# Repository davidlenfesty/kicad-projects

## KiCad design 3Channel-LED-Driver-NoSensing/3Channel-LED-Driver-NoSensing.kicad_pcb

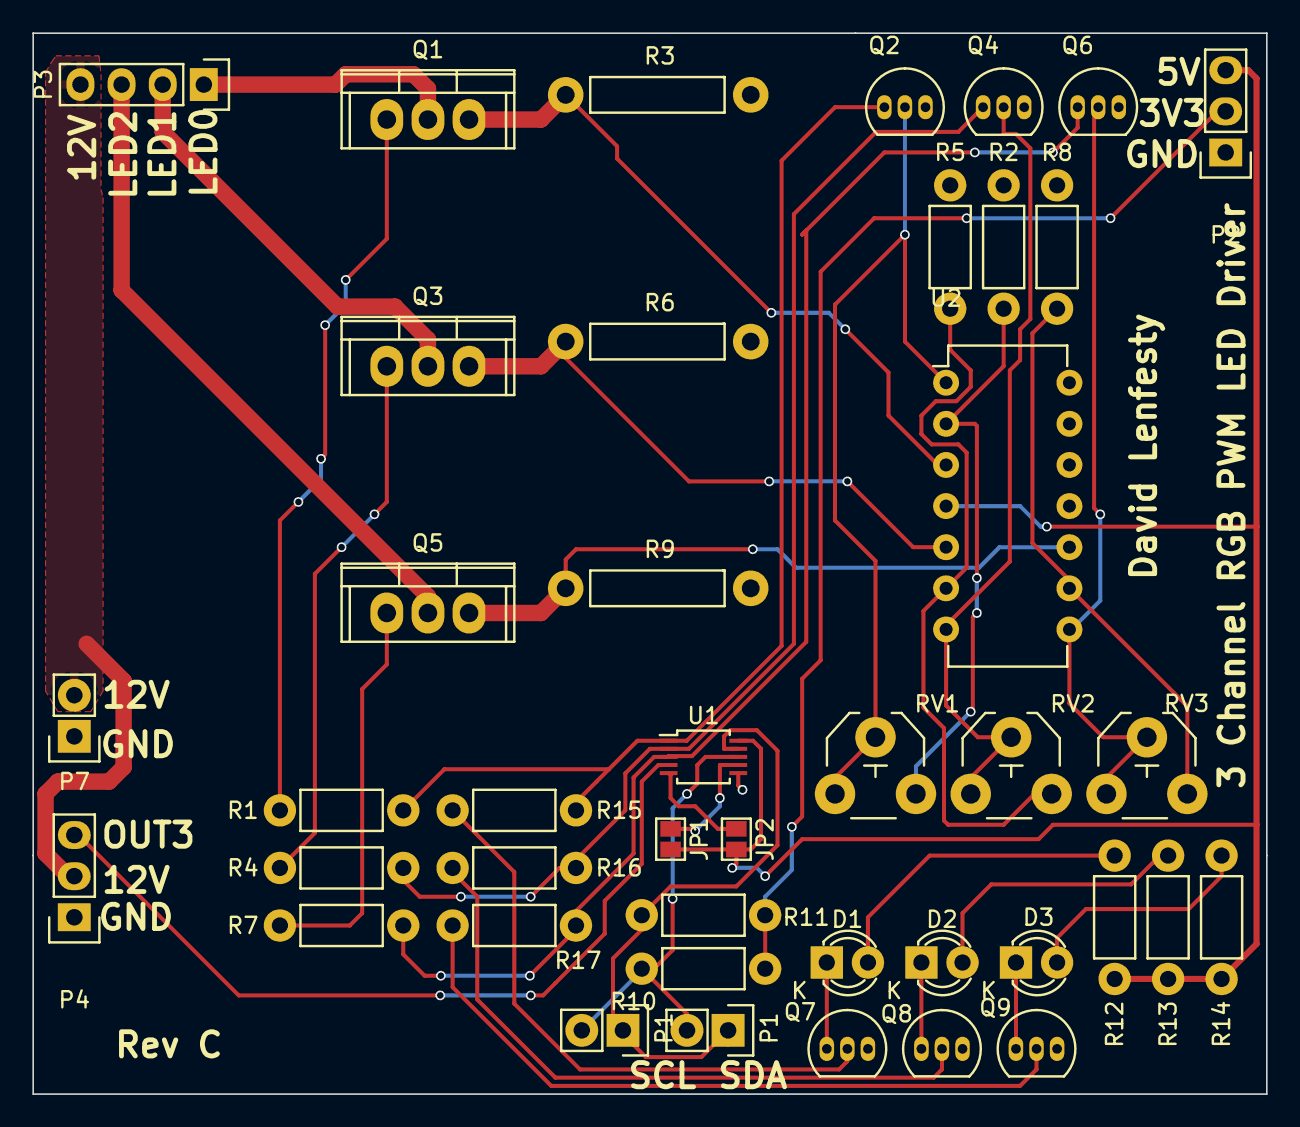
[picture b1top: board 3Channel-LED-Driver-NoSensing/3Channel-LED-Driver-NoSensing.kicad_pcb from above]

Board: 2 copper layers, 76.2 x 65.5 mm, 42 parts (0 on the bottom side), 36 nets.

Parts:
D1, D2, D3: LED; LED-3MM
JP1, JP2: Jumper_NO_Small; GS2
P1, P1#2, P7: CONN_01X02; Pin_Header_Straight_1x02
P2, P4: CONN_01X03; Pin_Header_Straight_1x03
P3: CONN_01X04; Pin_Header_Straight_1x04
Q1, Q3, Q5: BUT11A; TO-220
Q2, Q4, Q6, Q7, Q8, Q9: BC413; TO-92_Inline_Narrow_Oval
R1, R4, R7: 10K; Resistor_Horizontal_RM7mm
R2, R5, R8: 2K; Resistor_Horizontal_RM7mm
R3, R6, R9: R; Current_Sense_Resistor
R10, R11: 4.7K; Resistor_Horizontal_RM7mm
R12, R13, R14: 330; Resistor_Horizontal_RM7mm
R15, R16, R17: 50K; Resistor_Horizontal_RM7mm
RV1, RV2, RV3: 10K; Potentiometer_VishaySpectrol-Econtrim-Type36P
U1: PCA9633; TSSOP-10_3x3mm_Pitch0.5mm
U2: LM324AN; DIP-14_W7.62mm

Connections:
+3V3: P2.2, R10.2, R11.2
+5V: JP1.2, JP2.2, P2.3, R12.2, R13.1, R14.1, U1.10, U2.4
+12V: P3.4, P4.2, P7.2
GND: P2.1, P4.1, P7.1, Q2.3, Q4.3, Q6.3, Q7.3, Q8.3, Q9.3, R2.2, R3.2, R5.2, R6.2, R8.2, R9.2, U1.6, U2.11
LED0_IND: Q2.1, R1.2, R15.2, U1.1
LED1_IND: Q4.1, R4.2, R16.2, U1.2
LED2_IND: Q6.1, R7.2, R17.2, U1.3
unnamed: D1.1, Q7.1
unnamed: D1.2, R12.1
unnamed: D2.1, Q8.1
unnamed: D2.2, R13.2
unnamed: D3.1, Q9.1
unnamed: D3.2, R14.2
unnamed: JP1.1, U1.7
unnamed: JP2.1, U1.5
unnamed: P1.1, P1#2.1, R11.1, U1.9
unnamed: P1.2, P1#2.2, R10.1, U1.8
unnamed: P3.1, Q1.2
unnamed: P3.2, Q3.2
unnamed: P3.3, Q5.2
unnamed: P4.3, U1.4
unnamed: Q1.1, R1.1
unnamed: Q1.3, R3.1, U2.3
unnamed: Q2.2, RV1.1, RV1.2, U2.1
unnamed: Q3.1, R4.1
unnamed: Q3.3, R6.1, U2.5
unnamed: Q4.2, RV2.1, RV2.2, U2.7
unnamed: Q5.1, R7.1
unnamed: Q5.3, R9.1, U2.10
unnamed: Q6.2, RV3.1, RV3.2, U2.8
unnamed: Q7.2, R15.1
unnamed: Q8.2, R16.1
unnamed: Q9.2, R17.1
unnamed: R2.1, RV1.3, U2.2
unnamed: R5.1, RV2.3, U2.6
unnamed: R8.1, RV3.3, U2.9

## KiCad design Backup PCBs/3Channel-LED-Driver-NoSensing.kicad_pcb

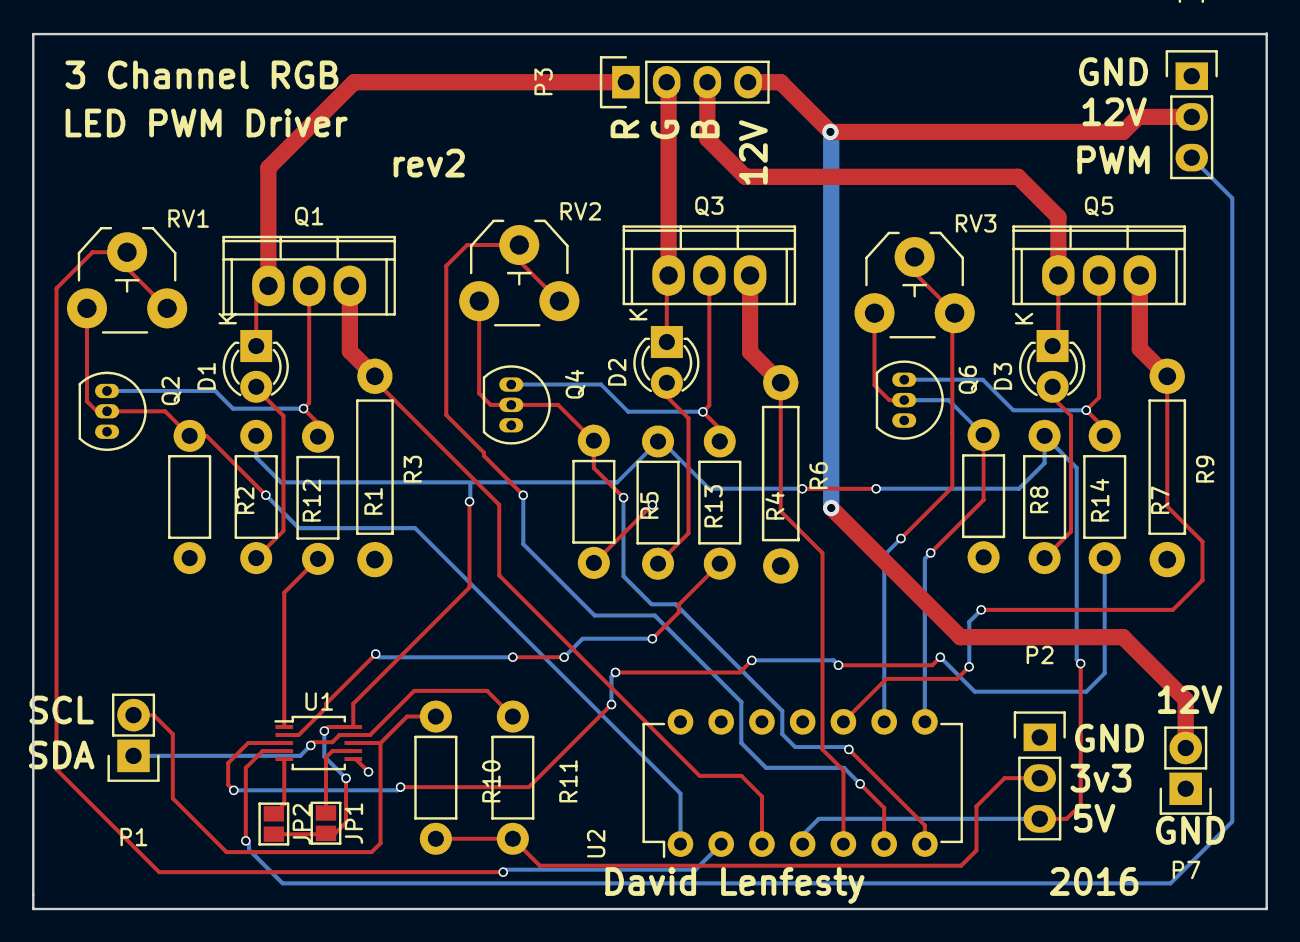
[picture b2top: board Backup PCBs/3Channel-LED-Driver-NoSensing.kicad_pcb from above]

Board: 2 copper layers, 76.9 x 54.6 mm, 35 parts (0 on the bottom side), 30 nets.

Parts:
D1, D2, D3: LED; LED-3MM
JP1, JP2: Jumper_NO_Small; GS2
P1, P7: CONN_01X02; Pin_Header_Straight_1x02
P2, P4: CONN_01X03; Pin_Header_Straight_1x03
P3: CONN_01X04; Pin_Header_Straight_1x04
Q1, Q3, Q5: BUZ11; TO-220
Q2, Q4, Q6: BC413; TO-92_Inline_Narrow_Oval
R1, R4, R7: 10K; Resistor_Horizontal_RM7mm
R2, R5, R8: 2K; Resistor_Horizontal_RM7mm
R3, R6, R9: R; Current_Sense_Resistor
R10, R11: 4.7K; Resistor_Horizontal_RM7mm
R12, R13, R14: 330; Resistor_Horizontal_RM7mm
RV1, RV2, RV3: 10K; Potentiometer_VishaySpectrol-Econtrim-Type36P
U1: PCA9633; TSSOP-10_3x3mm_Pitch0.5mm
U2: LM324AN; DIP-14_W7.62mm

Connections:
+3V3: P2.2, R10.2, R11.2
+5V: JP1.2, JP2.2, P2.3, R12.1, R13.1, R14.1, U1.10, U2.4
+12V: P3.4, P4.2, P7.2
GND: P2.1, P4.1, P7.1, Q2.3, Q4.3, Q6.3, R2.2, R3.2, R5.2, R6.2, R8.2, R9.2, U1.6, U2.11
unnamed: D1.1, P3.1, Q1.1
unnamed: D1.2, R12.2
unnamed: D2.1, P3.2, Q3.1
unnamed: D2.2, R13.2
unnamed: D3.1, P3.3, Q5.1
unnamed: D3.2, R14.2
unnamed: JP1.1, U1.7
unnamed: JP2.1, U1.5
unnamed: P1.1, R11.1, U1.9
unnamed: P1.2, R10.1, U1.8
unnamed: P4.3, U1.4
unnamed: Q1.2, Q2.1, R1.1
unnamed: Q1.3, R3.1, U2.3
unnamed: Q2.2, R2.1, RV1.1, U2.1
unnamed: Q3.2, Q4.1, R4.1
unnamed: Q3.3, R6.1, U2.5
unnamed: Q4.2, R5.1, RV2.1, U2.7
unnamed: Q5.2, Q6.1, R7.1
unnamed: Q5.3, R9.1, U2.10
unnamed: Q6.2, R8.1, RV3.1, U2.8
unnamed: R1.2, U1.1
unnamed: R4.2, U1.2
unnamed: R7.2, U1.3
unnamed: RV1.2, RV1.3, U2.2
unnamed: RV2.2, RV2.3, U2.6
unnamed: RV3.2, RV3.3, U2.9

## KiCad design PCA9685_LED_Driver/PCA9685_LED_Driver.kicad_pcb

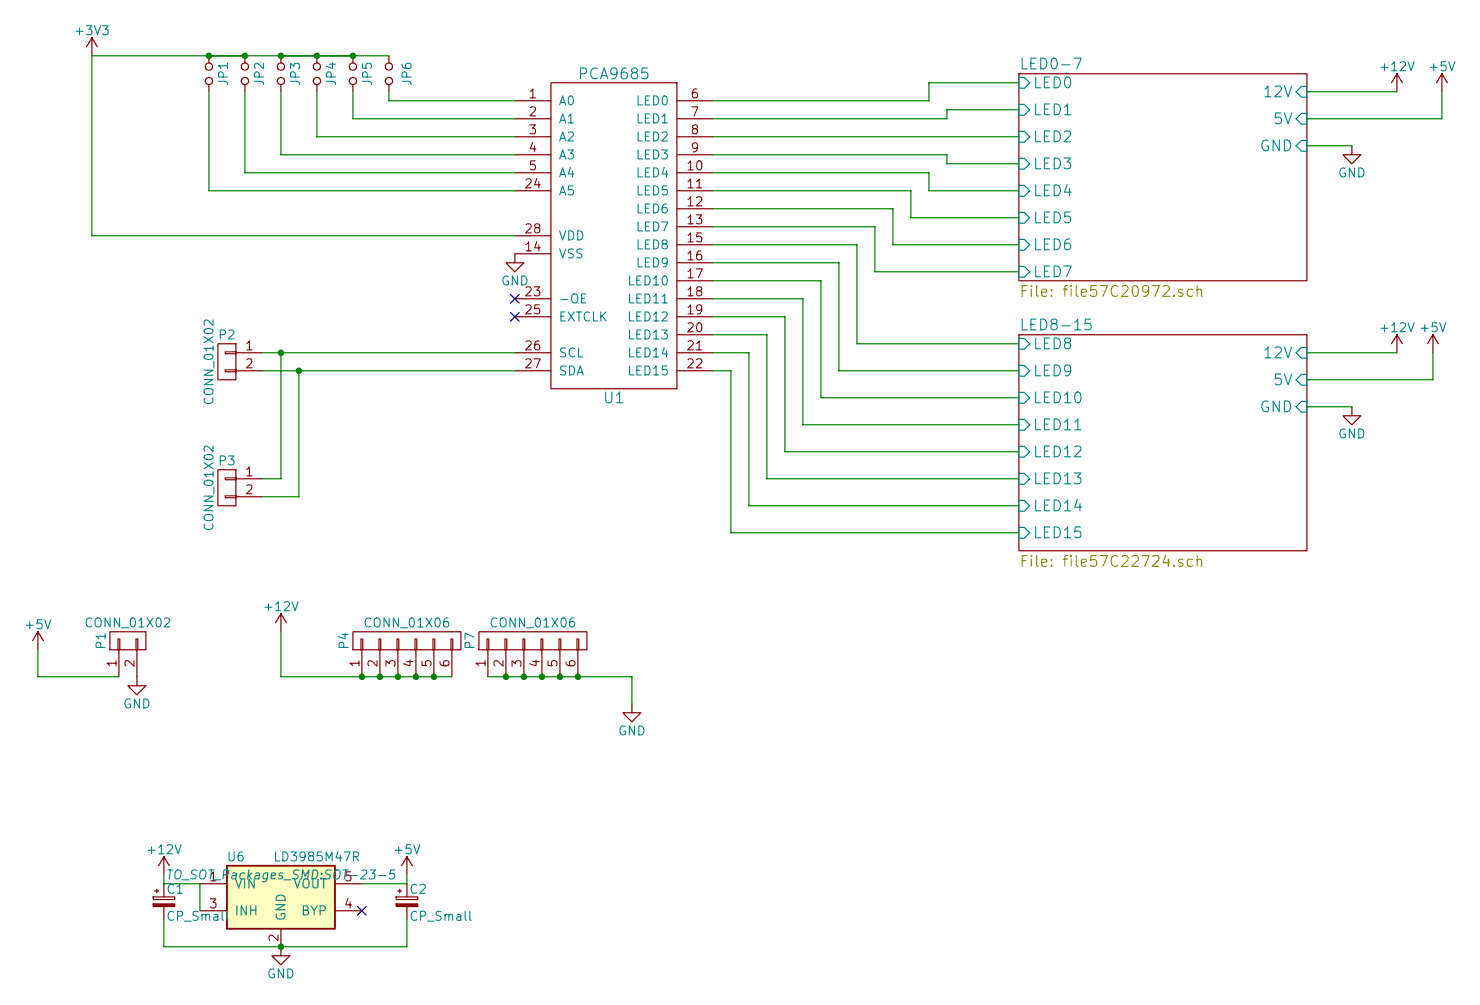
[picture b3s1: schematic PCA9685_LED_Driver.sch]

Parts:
C1, C2: CP_Small; TantalC_SizeA_EIA-3216_HandSoldering
JP1, JP2, JP3, JP4, JP5, JP6: Jumper_NO_Small; GS2
P1, P2, P3: CONN_01X02; Pin_Header_Straight_1x02
P4, P7: CONN_01X06; Screw_Connector_M5
U1: PCA9685; TSSOP-28_4.4x9.7mm_Pitch0.65mm
U6: LD3985M47R; SOT-23-5

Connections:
+3V3: JP1.1, JP2.1, JP3.1, JP4.1, JP5.1, JP6.1, U1.28 (VDD)
+5V: C2.1, P1.1, U6.5 (VOUT); also elsewhere on the board
+12V: C1.1, P4.1, P4.2, P4.3, P4.4, P4.5, P4.6, U6.1 (VIN), U6.3 (INH); also elsewhere on the board
/LED0-7/LED1: U1.7 (LED1); also elsewhere on the board
/LED0-7/LED2: U1.8 (LED2); also elsewhere on the board
/LED0-7/LED3: U1.9 (LED3); also elsewhere on the board
/LED0-7/LED4: U1.10 (LED4); also elsewhere on the board
/LED0-7/LED5: U1.11 (LED5); also elsewhere on the board
/LED0-7/LED6: U1.12 (LED6); also elsewhere on the board
/LED0-7/LED7: U1.13 (LED7); also elsewhere on the board
/LED8-15/LED8: U1.15 (LED8); also elsewhere on the board
/LED8-15/LED9: U1.16 (LED9); also elsewhere on the board
/LED8-15/LED10: U1.17 (LED10); also elsewhere on the board
/LED8-15/LED11: U1.18 (LED11); also elsewhere on the board
/LED8-15/LED12: U1.19 (LED12); also elsewhere on the board
/LED8-15/LED13: U1.20 (LED13); also elsewhere on the board
/LED8-15/LED14: U1.21 (LED14); also elsewhere on the board
/LED8-15/LED15: U1.22 (LED15); also elsewhere on the board
GND: C1.2, C2.2, P1.2, P7.1, P7.2, P7.3, P7.4, P7.5, P7.6, U1.14 (VSS), U6.2 (GND); also elsewhere on the board
unnamed: JP1.2, U1.24 (A5)
unnamed: JP2.2, U1.5 (A4)
unnamed: JP3.2, U1.4 (A3)
unnamed: JP4.2, U1.3 (A2)
unnamed: JP5.2, U1.2 (A1)
unnamed: JP6.2, U1.1 (A0)
unnamed: P2.1, P3.1, U1.26 (SCL)
unnamed: P2.2, P3.2, U1.27 (SDA)

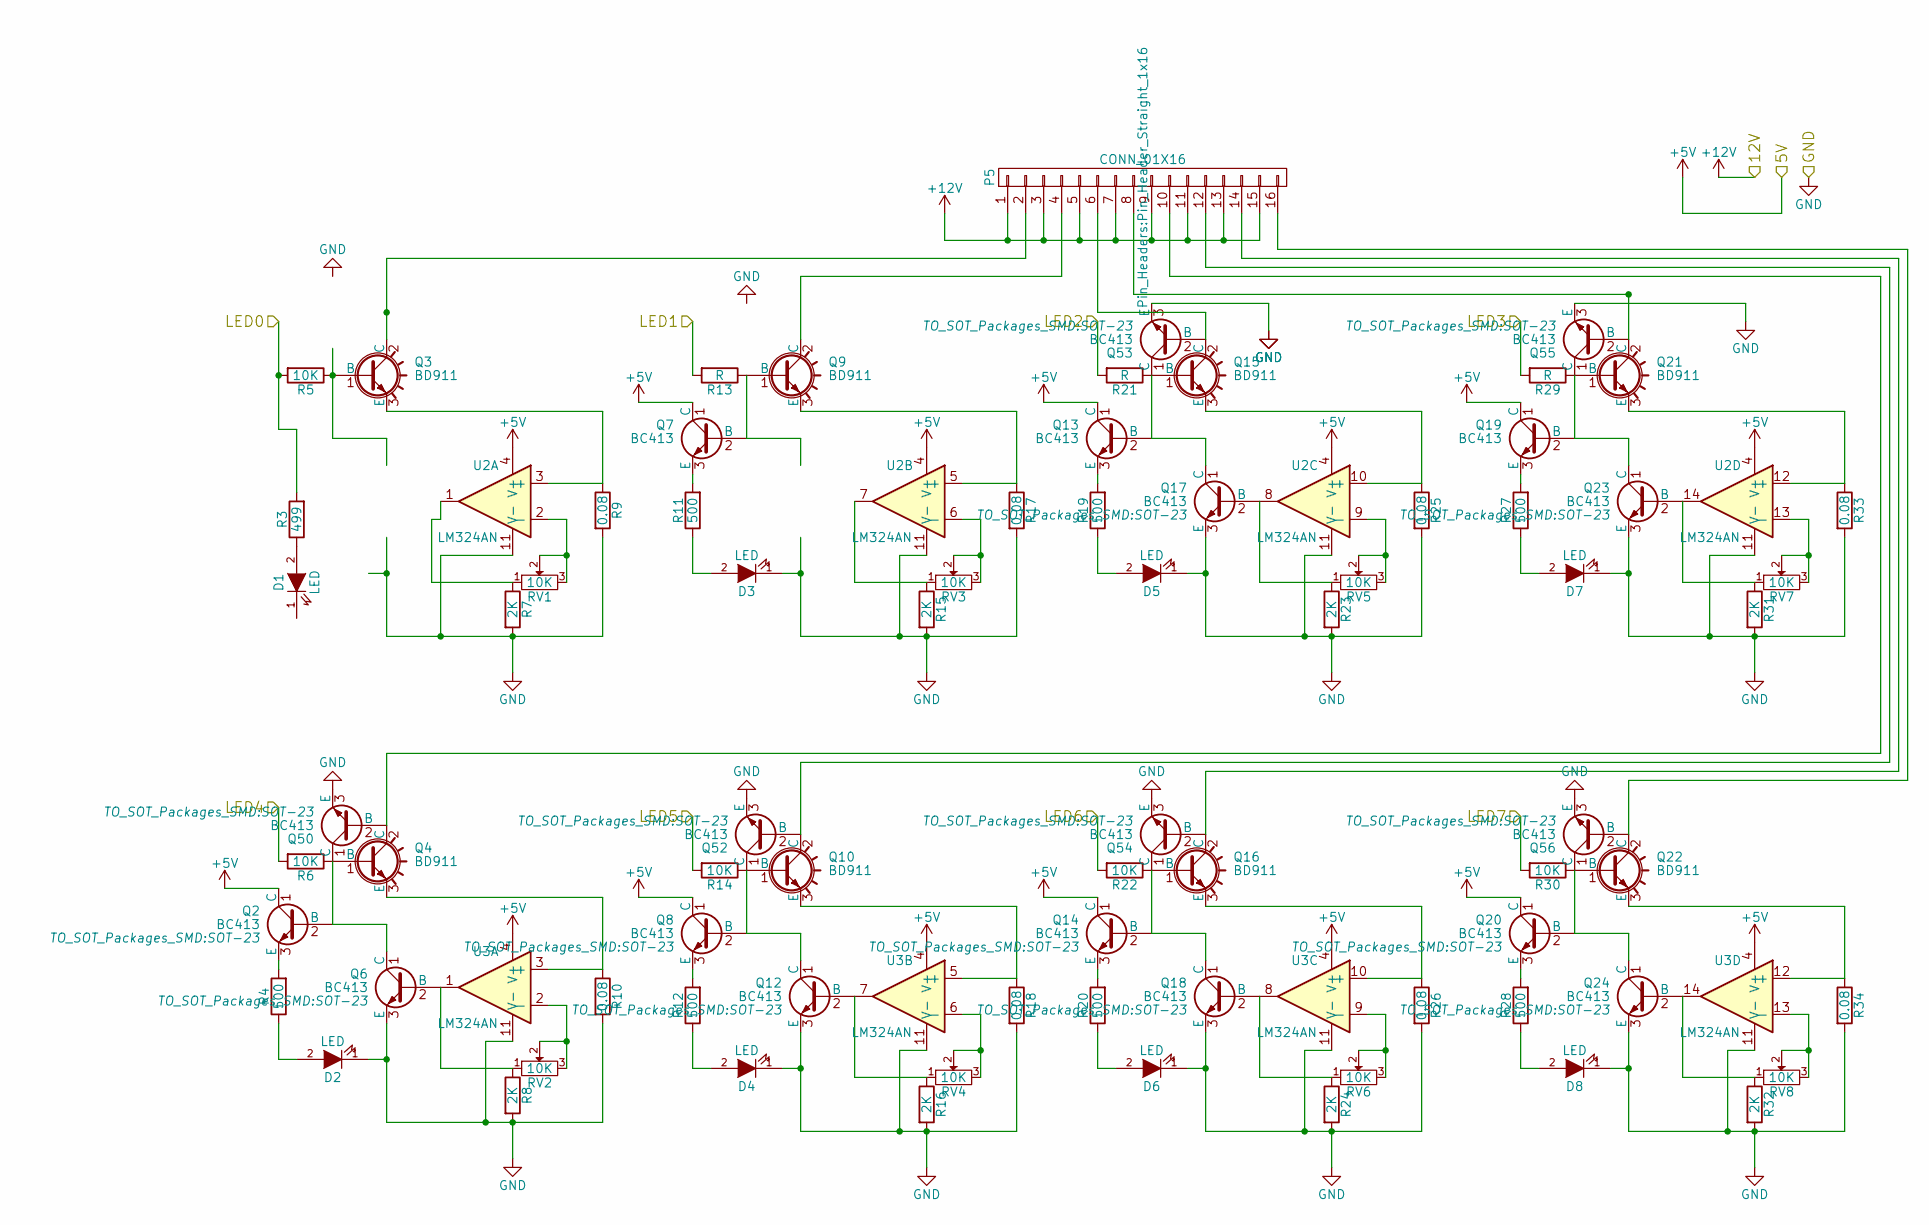
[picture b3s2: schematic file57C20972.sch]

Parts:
D1, D2, D3, D4, D5, D6, D7, D8: LED; LED_0805
P5: CONN_01X16; Pin_Header_Straight_1x16
Q2, Q6, Q7, Q8, Q12, Q13, Q14, Q17, Q18, Q19, Q20, Q23, Q24, Q50, Q52, Q53, Q54, Q55, Q56: BC413; SOT-23
Q3, Q4, Q9, Q10, Q15, Q16, Q21, Q22: BD911; TO-220_Neutral123_Vertical_LargePads
R3: 499; R_0805_HandSoldering
R4, R11, R12, R19, R20, R27, R28: 500; R_0805_HandSoldering
R5, R6, R14, R22, R30: 10K; R_0805_HandSoldering
R7, R8, R15, R16, R23, R24, R31, R32: 2K; R_0805_HandSoldering
R9, R10, R17, R18, R25, R26, R33, R34: 0.08; R_2816_HandSoldering
R13, R21, R29: R; R_0805_HandSoldering
RV1, RV2, RV3, RV4, RV5, RV6, RV7, RV8: 10K; SMD_Trim_Pot-(3.8X3.6)
U2, U3: LM324AN; SOIC-14_3.9x8.7mm_Pitch1.27mm

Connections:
+5V: Q2.1 (C), Q7.1 (C), Q8.1 (C), Q13.1 (C), Q14.1 (C), Q19.1 (C), Q20.1 (C), U2.4 (V+), U3.4 (V+); also elsewhere on the board
+12V: P5.1, P5.3, P5.5, P5.7, P5.9, P5.11, P5.13, P5.15; also elsewhere on the board
/LED0-7/LED1: R13.2; also elsewhere on the board
/LED0-7/LED2: R21.2; also elsewhere on the board
/LED0-7/LED3: R29.2; also elsewhere on the board
/LED0-7/LED4: R6.2; also elsewhere on the board
/LED0-7/LED5: R14.2; also elsewhere on the board
/LED0-7/LED6: R22.2; also elsewhere on the board
/LED0-7/LED7: R30.2; also elsewhere on the board
GND: D1.1 (K), D2.1 (K), D3.1 (K), D4.1 (K), D5.1 (K), D6.1 (K), D7.1 (K), D8.1 (K), Q6.3 (E), Q12.3 (E), Q17.3 (E), Q18.3 (E), Q23.3 (E), Q24.3 (E), Q50.3 (E), Q52.3 (E), Q53.3 (E), Q54.3 (E), Q55.3 (E), Q56.3 (E), R7.2, R8.2, R9.2, R10.2, R15.2, R16.2, R17.2, R18.2, R23.2, R24.2, R25.2, R26.2, R31.2, R32.2, R33.2, R34.2, U2.11 (V-), U3.11 (V-); also elsewhere on the board
unnamed: D1.2 (A), R3.1
unnamed: D2.2 (A), R4.1
unnamed: D3.2 (A), R11.1
unnamed: D4.2 (A), R12.1
unnamed: D5.2 (A), R19.1
unnamed: D6.2 (A), R20.1
unnamed: D7.2 (A), R27.1
unnamed: D8.2 (A), R28.1
unnamed 43: P5.2, Q3.2 (C); also elsewhere on the board
unnamed 44: P5.4, Q9.2 (C); also elsewhere on the board
unnamed: P5.6, Q15.2 (C), Q53.2 (B)
unnamed: P5.8, Q21.2 (C), Q55.2 (B)
unnamed: P5.10, Q4.2 (C), Q50.2 (B)
unnamed: P5.12, Q10.2 (C), Q52.2 (B)
unnamed: P5.14, Q16.2 (C), Q54.2 (B)
unnamed: P5.16, Q22.2 (C), Q56.2 (B)
unnamed 59: Q3.1 (B), R5.1; also elsewhere on the board
unnamed: Q2.2 (B), Q4.1 (B), Q6.1 (C), Q50.1 (C), R6.1
unnamed: Q2.3 (E), R4.2
unnamed: Q3.3 (E), R9.1, U2.3 (+)
unnamed: Q4.3 (E), R10.1, U3.3 (+)
unnamed 64: R7.1, RV1.1, U2.1; also elsewhere on the board
unnamed: Q6.2 (B), R8.1, RV2.1, U3.1
unnamed: Q7.3 (E), R11.2
unnamed: Q8.3 (E), R12.2
unnamed: Q9.3 (E), R17.1, U2.5 (+)
unnamed: Q8.2 (B), Q10.1 (B), Q12.1 (C), Q52.1 (C), R14.1
unnamed: Q10.3 (E), R18.1, U3.5 (+)
unnamed 71: Q7.2 (B), Q9.1 (B), R13.1; also elsewhere on the board
unnamed 72: R15.1, RV3.1, U2.7; also elsewhere on the board
unnamed: Q12.2 (B), R16.1, RV4.1, U3.7
unnamed: Q13.2 (B), Q15.1 (B), Q17.1 (C), Q53.1 (C), R21.1
unnamed: Q13.3 (E), R19.2
unnamed: Q14.2 (B), Q16.1 (B), Q18.1 (C), Q54.1 (C), R22.1
unnamed: Q14.3 (E), R20.2
unnamed: Q15.3 (E), R25.1, U2.10 (+)
unnamed: Q16.3 (E), R26.1, U3.10 (+)
unnamed: Q17.2 (B), R23.1, RV5.1, U2.8
unnamed: Q18.2 (B), R24.1, RV6.1, U3.8
unnamed: Q19.2 (B), Q21.1 (B), Q23.1 (C), Q55.1 (C), R29.1
unnamed: Q19.3 (E), R27.2
unnamed: Q20.2 (B), Q22.1 (B), Q24.1 (C), Q56.1 (C), R30.1
unnamed: Q20.3 (E), R28.2
unnamed: Q21.3 (E), R33.1, U2.12 (+)
unnamed: Q22.3 (E), R34.1, U3.12 (+)
unnamed: Q23.2 (B), R31.1, RV7.1, U2.14
unnamed: Q24.2 (B), R32.1, RV8.1, U3.14
unnamed: RV1.2, RV1.3, U2.2 (-)
unnamed: RV2.2, RV2.3, U3.2 (-)
unnamed: RV3.2, RV3.3, U2.6 (-)
unnamed: RV4.2, RV4.3, U3.6 (-)
unnamed: RV5.2, RV5.3, U2.9 (-)
unnamed: RV6.2, RV6.3, U3.9 (-)
unnamed: RV7.2, RV7.3, U2.13 (-)
unnamed: RV8.2, RV8.3, U3.13 (-)

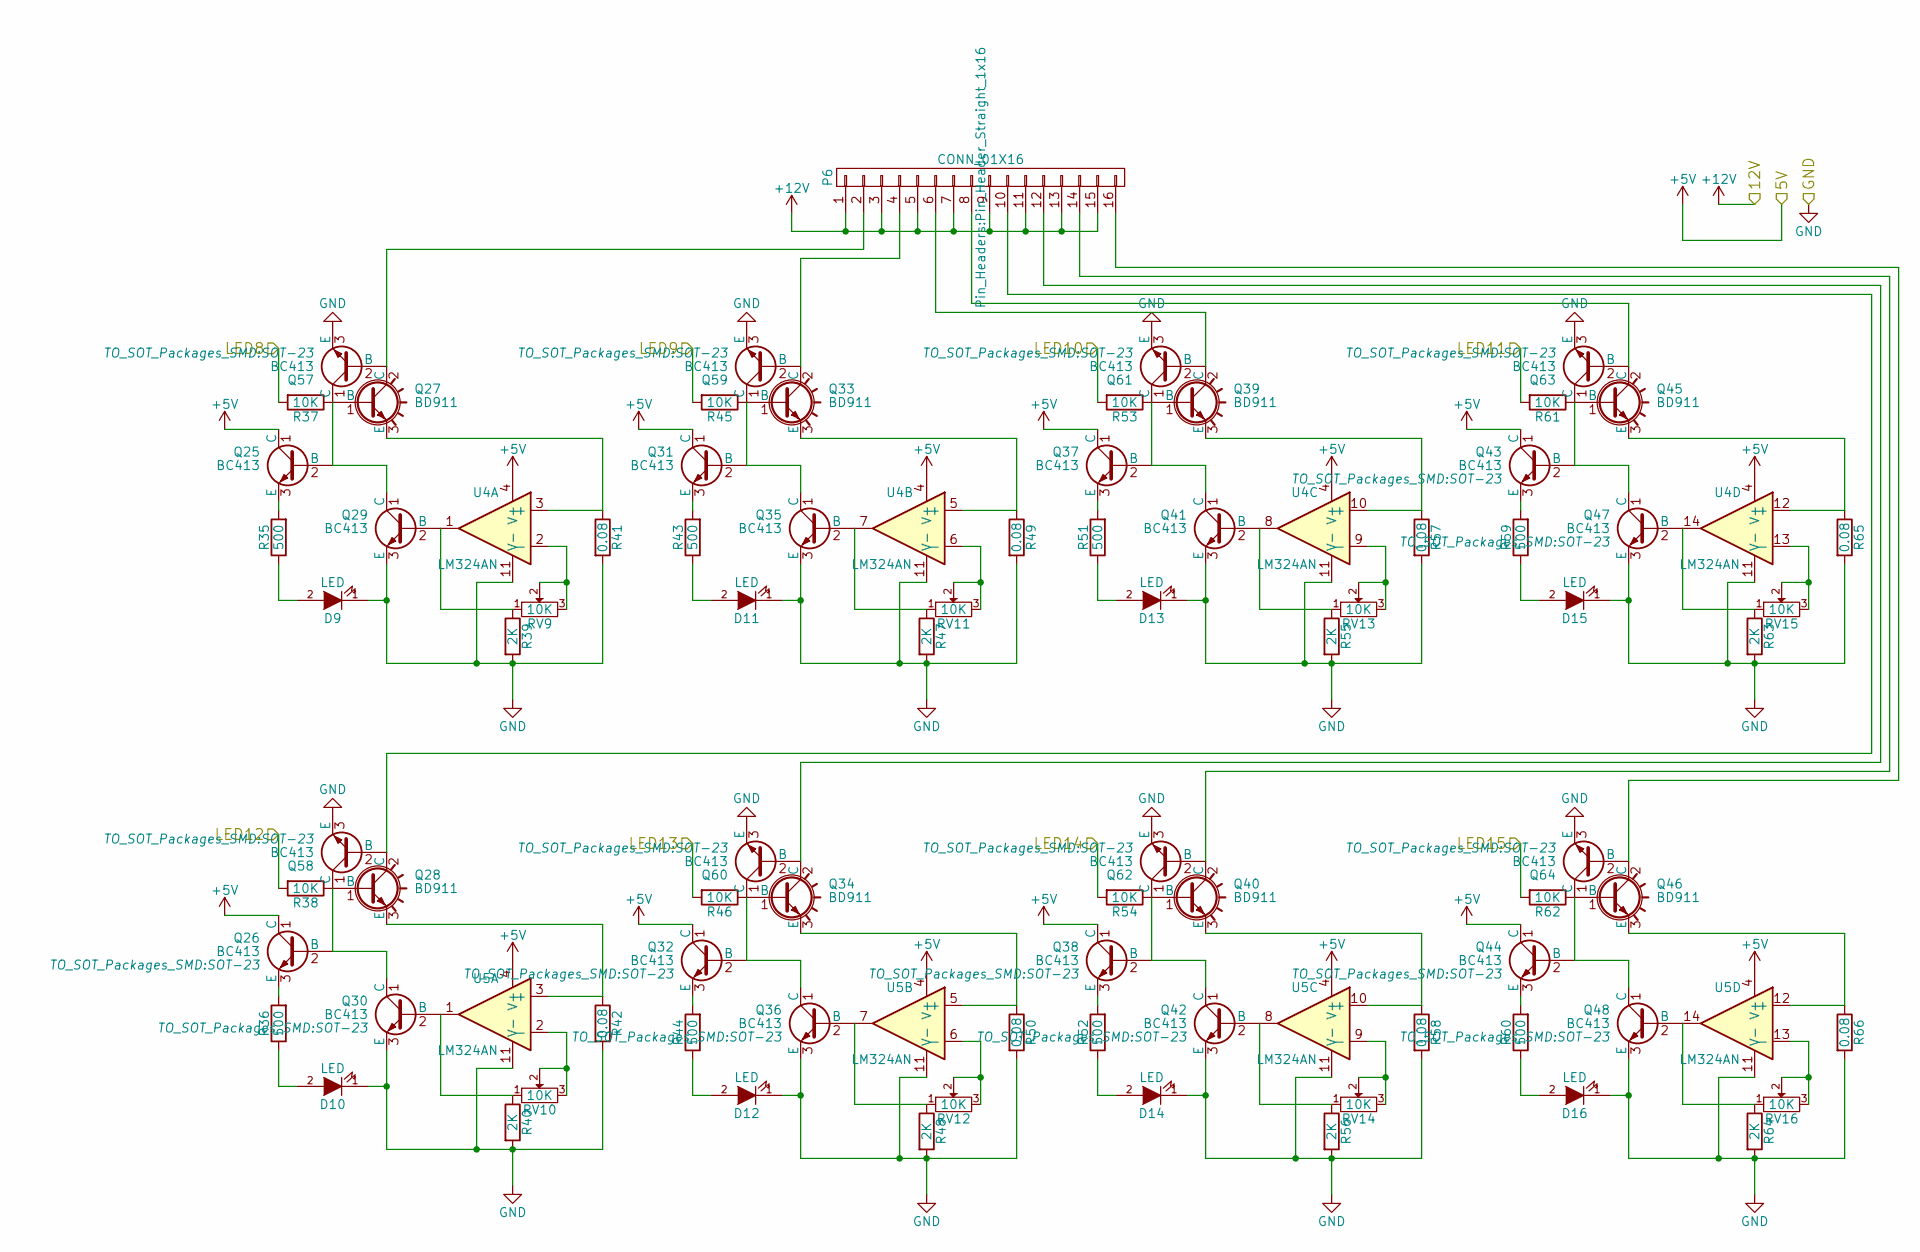
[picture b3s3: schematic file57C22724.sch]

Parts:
D9, D10, D11, D12, D13, D14, D15, D16: LED; LED_0805
P6: CONN_01X16; Pin_Header_Straight_1x16
Q25, Q26, Q29, Q30, Q31, Q32, Q35, Q36, Q37, Q38, Q41, Q42, Q43, Q44, Q47, Q48, Q57, Q58, Q59, Q60, Q61, Q62, Q63, Q64: BC413; SOT-23
Q27, Q28, Q33, Q34, Q39, Q40, Q45, Q46: BD911; TO-220_Neutral123_Vertical_LargePads
R35, R36, R43, R44, R51, R52, R59, R60: 500; R_0805_HandSoldering
R37, R38, R45, R46, R53, R54, R61, R62: 10K; R_0805_HandSoldering
R39, R40, R47, R48, R55, R56, R63, R64: 2K; R_0805_HandSoldering
R41, R42, R49, R50, R57, R58, R65, R66: 0.08; R_2816_HandSoldering
RV9, RV10, RV11, RV12, RV13, RV14, RV15, RV16: 10K; SMD_Trim_Pot-(3.8X3.6)
U4, U5: LM324AN; SOIC-14_3.9x8.7mm_Pitch1.27mm

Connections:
+5V: Q25.1 (C), Q26.1 (C), Q31.1 (C), Q32.1 (C), Q37.1 (C), Q38.1 (C), Q43.1 (C), Q44.1 (C), U4.4 (V+), U5.4 (V+); also elsewhere on the board
+12V: P6.1, P6.3, P6.5, P6.7, P6.9, P6.11, P6.13, P6.15; also elsewhere on the board
/LED8-15/LED8: R37.2; also elsewhere on the board
/LED8-15/LED9: R45.2; also elsewhere on the board
/LED8-15/LED10: R53.2; also elsewhere on the board
/LED8-15/LED11: R61.2; also elsewhere on the board
/LED8-15/LED12: R38.2; also elsewhere on the board
/LED8-15/LED13: R46.2; also elsewhere on the board
/LED8-15/LED14: R54.2; also elsewhere on the board
/LED8-15/LED15: R62.2; also elsewhere on the board
GND: D9.1 (K), D10.1 (K), D11.1 (K), D12.1 (K), D13.1 (K), D14.1 (K), D15.1 (K), D16.1 (K), Q29.3 (E), Q30.3 (E), Q35.3 (E), Q36.3 (E), Q41.3 (E), Q42.3 (E), Q47.3 (E), Q48.3 (E), Q57.3 (E), Q58.3 (E), Q59.3 (E), Q60.3 (E), Q61.3 (E), Q62.3 (E), Q63.3 (E), Q64.3 (E), R39.2, R40.2, R41.2, R42.2, R47.2, R48.2, R49.2, R50.2, R55.2, R56.2, R57.2, R58.2, R63.2, R64.2, R65.2, R66.2, U4.11 (V-), U5.11 (V-); also elsewhere on the board
unnamed: D9.2 (A), R35.1
unnamed: D10.2 (A), R36.1
unnamed: D11.2 (A), R43.1
unnamed: D12.2 (A), R44.1
unnamed: D13.2 (A), R51.1
unnamed: D14.2 (A), R52.1
unnamed: D15.2 (A), R59.1
unnamed: D16.2 (A), R60.1
unnamed: P6.2, Q27.2 (C), Q57.2 (B)
unnamed: P6.4, Q33.2 (C), Q59.2 (B)
unnamed: P6.6, Q39.2 (C), Q61.2 (B)
unnamed: P6.8, Q45.2 (C), Q63.2 (B)
unnamed: P6.10, Q28.2 (C), Q58.2 (B)
unnamed: P6.12, Q34.2 (C), Q60.2 (B)
unnamed: P6.14, Q40.2 (C), Q62.2 (B)
unnamed: P6.16, Q46.2 (C), Q64.2 (B)
unnamed: Q25.2 (B), Q27.1 (B), Q29.1 (C), Q57.1 (C), R37.1
unnamed: Q25.3 (E), R35.2
unnamed: Q26.2 (B), Q28.1 (B), Q30.1 (C), Q58.1 (C), R38.1
unnamed: Q26.3 (E), R36.2
unnamed: Q27.3 (E), R41.1, U4.3 (+)
unnamed: Q28.3 (E), R42.1, U5.3 (+)
unnamed: Q29.2 (B), R39.1, RV9.1, U4.1
unnamed: Q30.2 (B), R40.1, RV10.1, U5.1
unnamed: Q31.2 (B), Q33.1 (B), Q35.1 (C), Q59.1 (C), R45.1
unnamed: Q31.3 (E), R43.2
unnamed: Q32.2 (B), Q34.1 (B), Q36.1 (C), Q60.1 (C), R46.1
unnamed: Q32.3 (E), R44.2
unnamed: Q33.3 (E), R49.1, U4.5 (+)
unnamed: Q34.3 (E), R50.1, U5.5 (+)
unnamed: Q35.2 (B), R47.1, RV11.1, U4.7
unnamed: Q36.2 (B), R48.1, RV12.1, U5.7
unnamed: Q37.2 (B), Q39.1 (B), Q41.1 (C), Q61.1 (C), R53.1
unnamed: Q37.3 (E), R51.2
unnamed: Q38.2 (B), Q40.1 (B), Q42.1 (C), Q62.1 (C), R54.1
unnamed: Q38.3 (E), R52.2
unnamed: Q39.3 (E), R57.1, U4.10 (+)
unnamed: Q40.3 (E), R58.1, U5.10 (+)
unnamed: Q41.2 (B), R55.1, RV13.1, U4.8
unnamed: Q42.2 (B), R56.1, RV14.1, U5.8
unnamed: Q43.2 (B), Q45.1 (B), Q47.1 (C), Q63.1 (C), R61.1
unnamed: Q43.3 (E), R59.2
unnamed: Q44.2 (B), Q46.1 (B), Q48.1 (C), Q64.1 (C), R62.1
unnamed: Q44.3 (E), R60.2
unnamed: Q45.3 (E), R65.1, U4.12 (+)
unnamed: Q46.3 (E), R66.1, U5.12 (+)
unnamed: Q47.2 (B), R63.1, RV15.1, U4.14
unnamed: Q48.2 (B), R64.1, RV16.1, U5.14
unnamed: RV9.2, RV9.3, U4.2 (-)
unnamed: RV10.2, RV10.3, U5.2 (-)
unnamed: RV11.2, RV11.3, U4.6 (-)
unnamed: RV12.2, RV12.3, U5.6 (-)
unnamed: RV13.2, RV13.3, U4.9 (-)
unnamed: RV14.2, RV14.3, U5.9 (-)
unnamed: RV15.2, RV15.3, U4.13 (-)
unnamed: RV16.2, RV16.3, U5.13 (-)

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
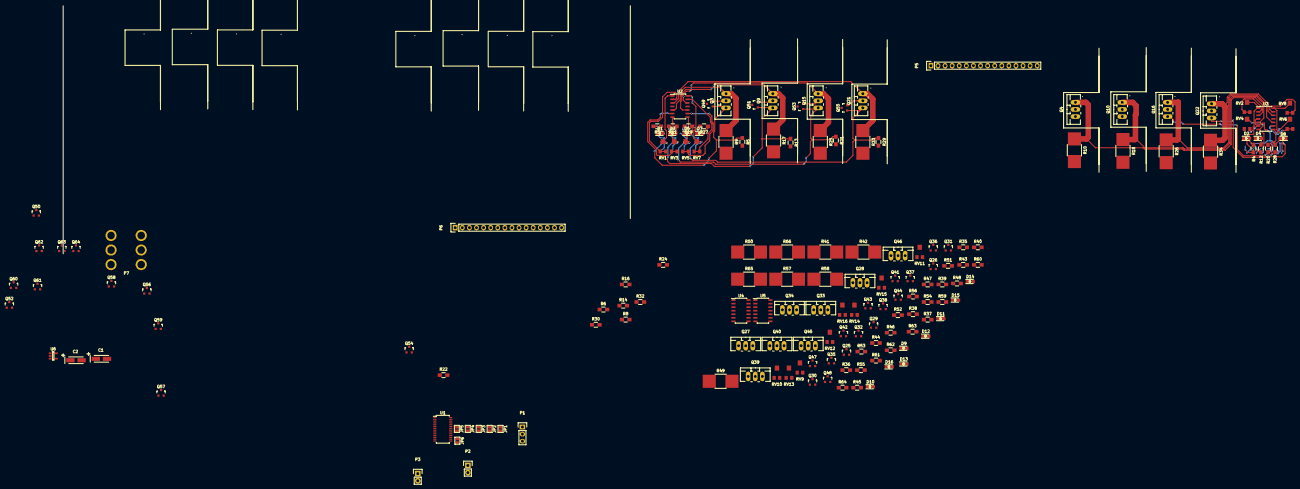
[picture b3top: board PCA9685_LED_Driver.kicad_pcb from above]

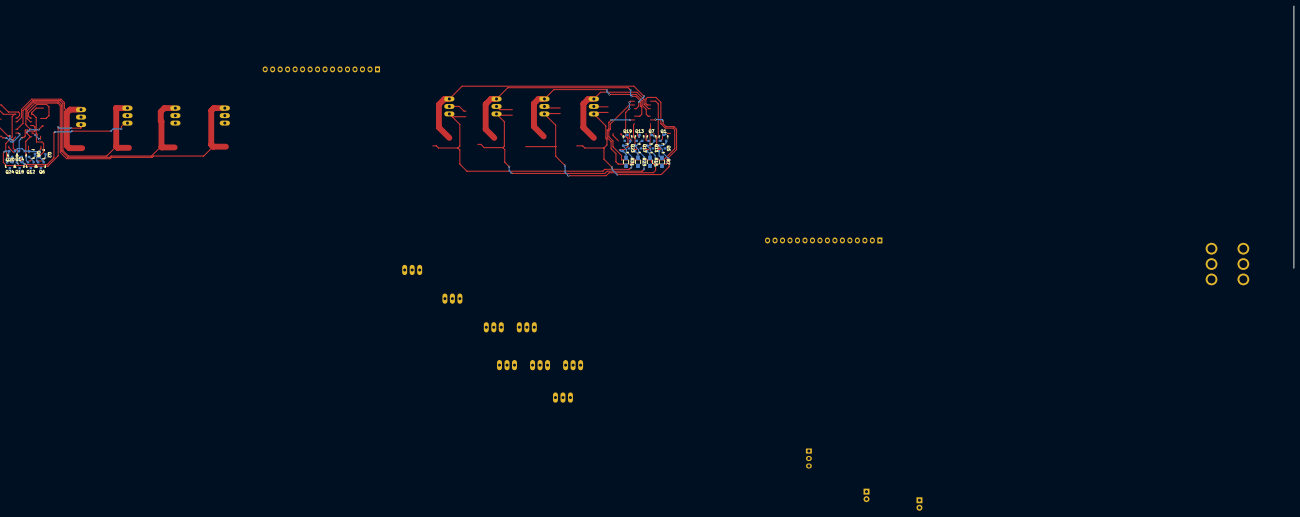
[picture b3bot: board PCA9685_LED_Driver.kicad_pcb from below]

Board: 2 copper layers, 179 parts (20 on the bottom side), 139 nets.

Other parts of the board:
Q1, Q5, Q11, Q49, Q51: BC413; SOT-23

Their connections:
+5V: Q1.1; also elsewhere on the board
GND: Q5.3, Q11.3, Q49.3, Q51.3; also elsewhere on the board
unnamed 43: Q49.2; also elsewhere on the board
unnamed 44: Q51.2; also elsewhere on the board
unnamed 59: Q1.2, Q5.1, Q49.1; also elsewhere on the board
unnamed 64: Q5.2; also elsewhere on the board
unnamed 71: Q11.1, Q51.1; also elsewhere on the board
unnamed 72: Q11.2; also elsewhere on the board

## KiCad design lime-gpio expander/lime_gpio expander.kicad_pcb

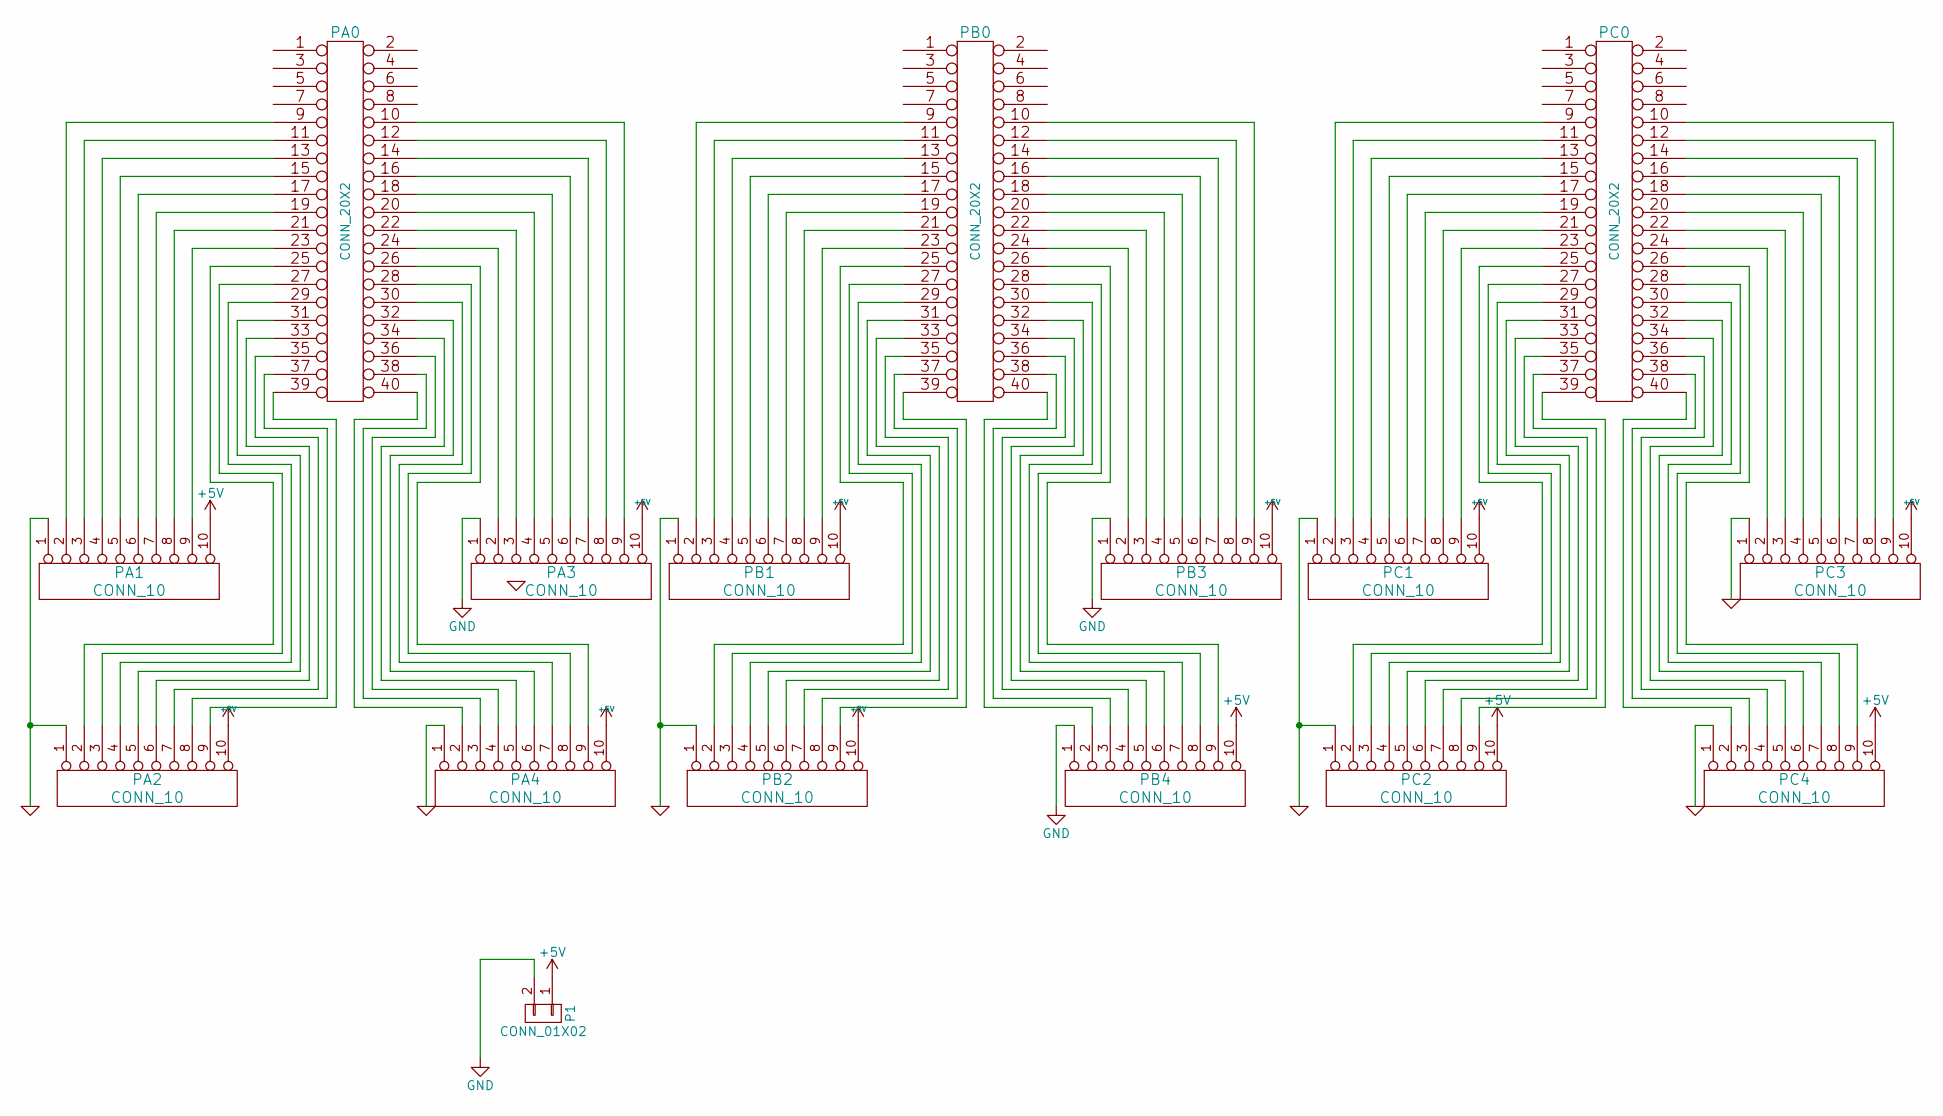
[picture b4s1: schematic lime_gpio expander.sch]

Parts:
P1: CONN_01X02; Pin_Header_Straight_1x02
PA0: CONN_20X2; SMDPinHeaders_2X20_1.27pitch
PA1, PA2, PA3, PA4: CONN_10; Pin_Header_Straight_1x10
PB0: CONN_20X2; SMDPinHeaders_2X20_1.27pitch
PB1, PB2, PB3, PB4: CONN_10; Pin_Header_Straight_1x10
PC0: CONN_20X2; SMDPinHeaders_2X20_1.27pitch
PC1, PC2, PC3, PC4: CONN_10; Pin_Header_Straight_1x10

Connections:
+5V: P1.1, PA1.10, PA2.10, PA3.10, PA4.10, PB1.10, PB2.10, PB3.10, PB4.10, PC1.10, PC2.10, PC3.10, PC4.10
GND: P1.2, PA1.1, PA2.1, PA3.1, PA4.1, PB1.1, PB2.1, PB3.1, PB4.1, PC1.1, PC2.1, PC3.1, PC4.1
unnamed: PA0.9, PA1.2
unnamed: PA0.10, PA3.9
unnamed: PA0.11, PA1.3
unnamed: PA0.12, PA3.8
unnamed: PA0.13, PA1.4
unnamed: PA0.14, PA3.7
unnamed: PA0.15, PA1.5
unnamed: PA0.16, PA3.6
unnamed: PA0.17, PA1.6
unnamed: PA0.18, PA3.5
unnamed: PA0.19, PA1.7
unnamed: PA0.20, PA3.4
unnamed: PA0.21, PA1.8
unnamed: PA0.22, PA3.3
unnamed: PA0.23, PA1.9
unnamed: PA0.24, PA3.2
unnamed: PA0.25, PA2.2
unnamed: PA0.26, PA4.9
unnamed: PA0.27, PA2.3
unnamed: PA0.28, PA4.8
unnamed: PA0.29, PA2.4
unnamed: PA0.30, PA4.7
unnamed: PA0.31, PA2.5
unnamed: PA0.32, PA4.6
unnamed: PA0.33, PA2.6
unnamed: PA0.34, PA4.5
unnamed: PA0.35, PA2.7
unnamed: PA0.36, PA4.4
unnamed: PA0.37, PA2.8
unnamed: PA0.38, PA4.3
unnamed: PA0.39, PA2.9
unnamed: PA0.40, PA4.2
unnamed: PB0.9, PB1.2
unnamed: PB0.10, PB3.9
unnamed: PB0.11, PB1.3
unnamed: PB0.12, PB3.8
unnamed: PB0.13, PB1.4
unnamed: PB0.14, PB3.7
unnamed: PB0.15, PB1.5
unnamed: PB0.16, PB3.6
unnamed: PB0.17, PB1.6
unnamed: PB0.18, PB3.5
unnamed: PB0.19, PB1.7
unnamed: PB0.20, PB3.4
unnamed: PB0.21, PB1.8
unnamed: PB0.22, PB3.3
unnamed: PB0.23, PB1.9
unnamed: PB0.24, PB3.2
unnamed: PB0.25, PB2.2
unnamed: PB0.26, PB4.9
unnamed: PB0.27, PB2.3
unnamed: PB0.28, PB4.8
unnamed: PB0.29, PB2.4
unnamed: PB0.30, PB4.7
unnamed: PB0.31, PB2.5
unnamed: PB0.32, PB4.6
unnamed: PB0.33, PB2.6
unnamed: PB0.34, PB4.5
unnamed: PB0.35, PB2.7
unnamed: PB0.36, PB4.4
unnamed: PB0.37, PB2.8
unnamed: PB0.38, PB4.3
unnamed: PB0.39, PB2.9
unnamed: PB0.40, PB4.2
unnamed: PC0.9, PC1.2
unnamed: PC0.10, PC3.9
unnamed: PC0.11, PC1.3
unnamed: PC0.12, PC3.8
unnamed: PC0.13, PC1.4
unnamed: PC0.14, PC3.7
unnamed: PC0.15, PC1.5
unnamed: PC0.16, PC3.6
unnamed: PC0.17, PC1.6
unnamed: PC0.18, PC3.5
unnamed: PC0.19, PC1.7
unnamed: PC0.20, PC3.4
unnamed: PC0.21, PC1.8
unnamed: PC0.22, PC3.3
unnamed: PC0.23, PC1.9
unnamed: PC0.24, PC3.2
unnamed: PC0.25, PC2.2
unnamed: PC0.26, PC4.9
unnamed: PC0.27, PC2.3
unnamed: PC0.28, PC4.8
unnamed: PC0.29, PC2.4
unnamed: PC0.30, PC4.7
unnamed: PC0.31, PC2.5
unnamed: PC0.32, PC4.6
unnamed: PC0.33, PC2.6
unnamed: PC0.34, PC4.5
unnamed: PC0.35, PC2.7
unnamed: PC0.36, PC4.4
unnamed: PC0.37, PC2.8
unnamed: PC0.38, PC4.3
unnamed: PC0.39, PC2.9
unnamed: PC0.40, PC4.2
